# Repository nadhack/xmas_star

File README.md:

# WiFi connected Christmas Star
Hardware and software for the WiFi connected Christmas star project

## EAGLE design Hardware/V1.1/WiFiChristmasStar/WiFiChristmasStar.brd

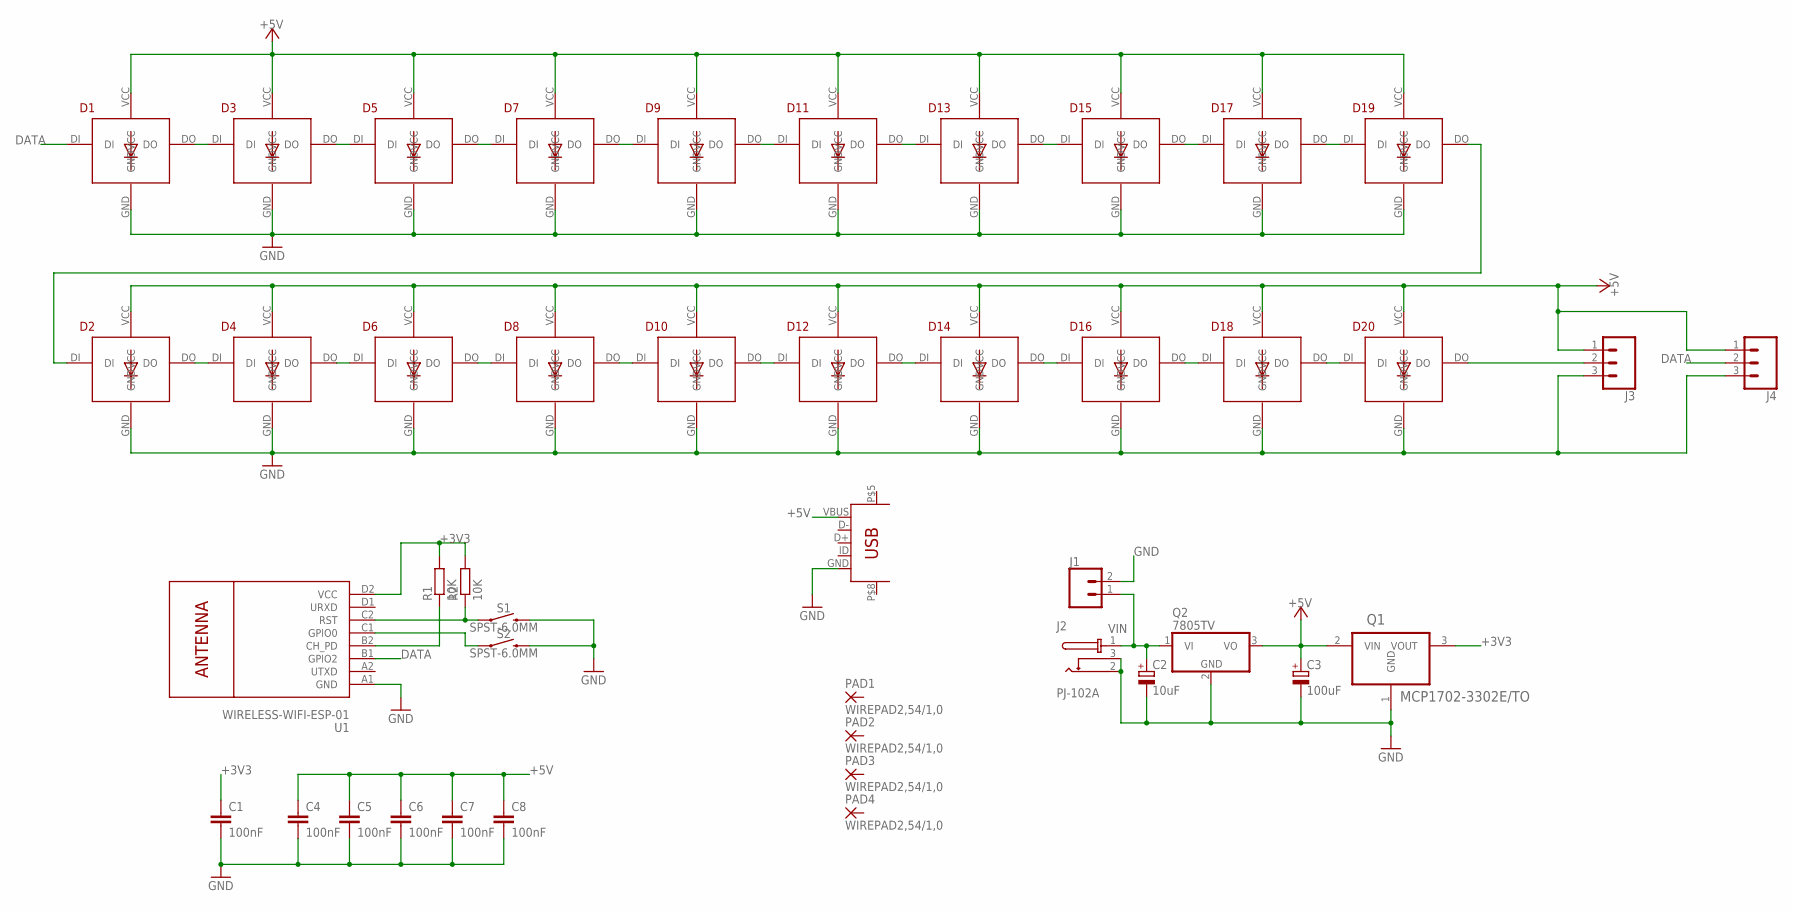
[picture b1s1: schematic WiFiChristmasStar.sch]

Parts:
C1, C4, C5, C6, C7, C8: 100nF; C025-025X050
C2: 10uF; E2,5-6
C3: 100uF; E2,5-6
CON1: MOLEX-548190519-MICROUSB; MOLEX-548190519
D1, D2, D3, D4, D5, D6, D7, D8, D9, D10, D11, D12, D13, D14, D15, D16, D17, D18, D19, D20: APA-106; LED5MMRGB
J1: CONN_023.5MM; SCREWTERMINAL-3.5MM-2
J2: PJ-102A; CUI_PJ-102A
J3, J4: CONN_03SCREW; SCREWTERMINAL-3.5MM-3
PAD1, PAD2, PAD3, PAD4: WIREPAD2,54/1,0; 2,54/1,0
Q1: MCP1702-3302E/TO; TO127P254X533-3
Q2: 7805TV; TO220V
R1, R2: 10K; 0204/7
S1, S2: SPST-6.0MM; TACTILE_SWITCH_PTH_6.0MM
U1: WIRELESS-WIFI-ESP-01

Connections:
+3V3: C1.1, Q1.3 (VOUT), R1.2, R2.2, U1.D2 (VCC)
+5V: C3.+, C4.1, C5.1, C6.1, C7.1, C8.1, CON1.VBUS, D1.VCC, D2.VCC, D3.VCC, D4.VCC, D5.VCC, D6.VCC, D7.VCC, D8.VCC, D9.VCC, D10.VCC, D11.VCC, D12.VCC, D13.VCC, D14.VCC, D15.VCC, D16.VCC, D17.VCC, D18.VCC, D19.VCC, D20.VCC, J3.1, J4.1, Q1.2 (VIN), Q2.3 (VO)
DATA: D1.DI, J4.2, U1.B1 (GPIO2)
GND: C1.2, C2.-, C3.-, C4.2, C5.2, C6.2, C7.2, C8.2, CON1.GND, D1.GND, D2.GND, D3.GND, D4.GND, D5.GND, D6.GND, D7.GND, D8.GND, D9.GND, D10.GND, D11.GND, D12.GND, D13.GND, D14.GND, D15.GND, D16.GND, D17.GND, D18.GND, D19.GND, D20.GND, J1.2, J2.2, J2.3, J3.3, J4.3, Q1.1 (GND), Q2.2 (GND), S1.3 (2), S2.3 (2), U1.A1 (GND)
unnamed: S2.1, U1.C1 (GPIO0)
unnamed: D2.DO, D4.DI
unnamed: D4.DO, D6.DI
unnamed: R1.1, U1.B2 (CH_PD)
unnamed: R2.1, S1.1, U1.C2 (RST)
unnamed: D6.DO, D8.DI
unnamed: D8.DO, D10.DI
unnamed: D2.DI, D19.DO
unnamed: D10.DO, D12.DI
unnamed: D12.DO, D14.DI
unnamed: D14.DO, D16.DI
unnamed: D16.DO, D18.DI
unnamed: D18.DO, D20.DI
unnamed: D20.DO, J3.2
unnamed: D1.DO, D3.DI
unnamed: D17.DO, D19.DI
unnamed: D15.DO, D17.DI
unnamed: D13.DO, D15.DI
unnamed: D11.DO, D13.DI
unnamed: D9.DO, D11.DI
unnamed: D7.DO, D9.DI
unnamed: D5.DO, D7.DI
unnamed: D3.DO, D5.DI
VIN: C2.+, J1.1, J2.1, Q2.1 (VI)

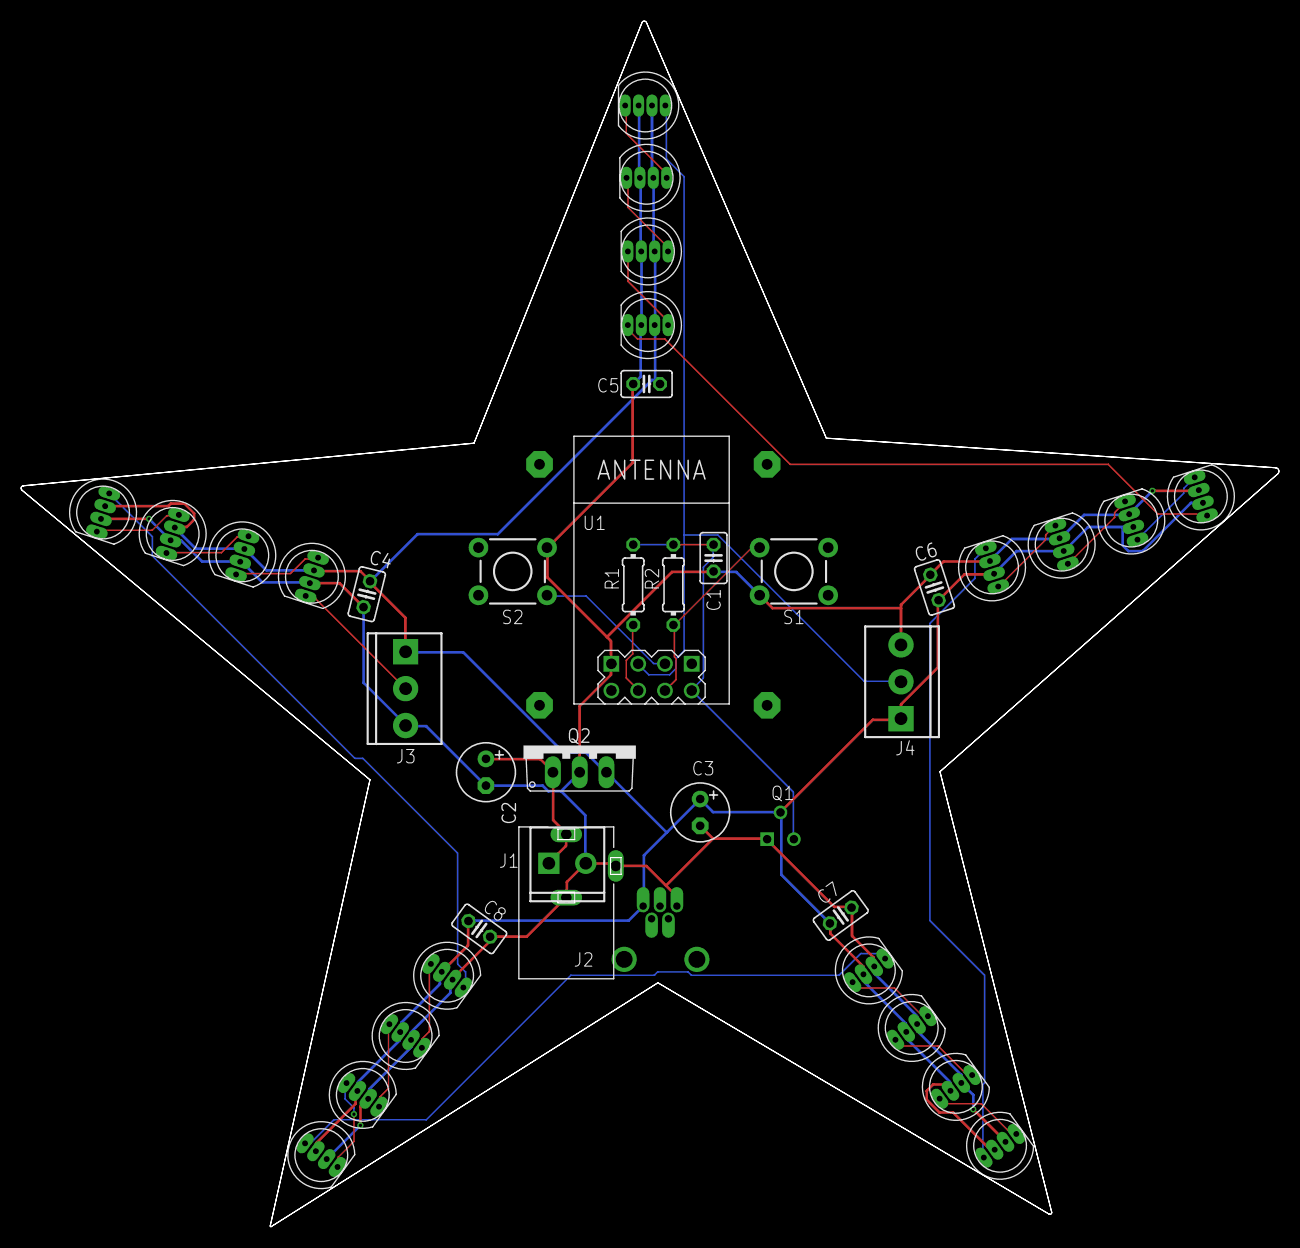
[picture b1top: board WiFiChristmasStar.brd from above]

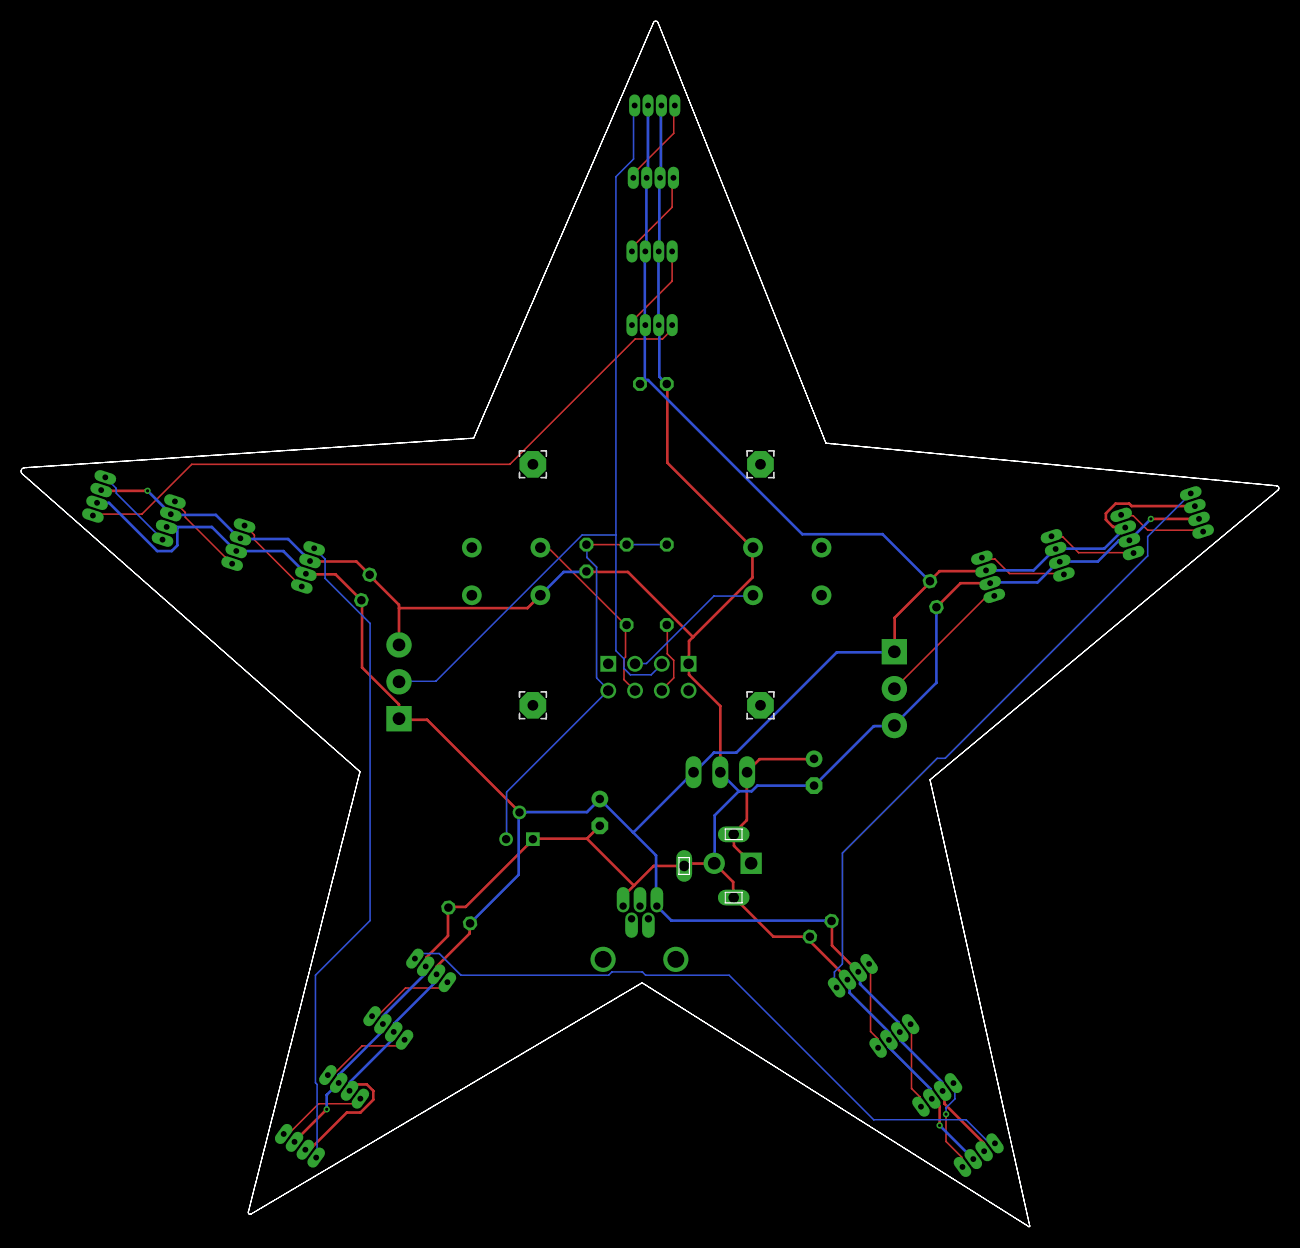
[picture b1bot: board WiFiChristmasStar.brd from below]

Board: 2 copper layers, 119.3 x 114.4 mm, 44 parts (4 on the bottom side), 28 nets.

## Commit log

2018-11-25 Added example sketches
2018-11-25 Added V1.1 hardware
    Files are for EagleCAD
2018-11-29 Added pdf schematic
2018-12-01 Updated to continuously show pattern until button pressed and released
2018-12-01 Added random point mode
2018-12-09 New sketches
    Multi-star and MQTT control
2018-12-09 removed
2019-12-19 Add ESPHome config

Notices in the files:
parts and their libraries:
SparkFun-Switches: Licensing: Creative Commons ShareAlike 4.0 International - https://creativecommons.org/licenses/by-sa/4.0
diy-modules: Released under the Creative Commons Attribution 4.0 International License: http://creativecommons.org/licenses/by/4.0
